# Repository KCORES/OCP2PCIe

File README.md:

# OCP2PCIe
 OCP 夹层网卡转标准 PCIe 槽转接卡设计  
 OCP Mezzanine card V2.0 to standard PCIe slot adapter design

 KCORES HomeLab 交流群 826702309

# For User
**用户指南**  

如果你想快速制作自己的OCP转接卡，请到[发行页面](https://github.com/KCORES/OCP2PCIe/releases)下载已发布的 Gerber 文件包  
并按[用户指南](doc/UserGuide_zh.md)准备相应的零件

If you want to build a OCP2PCIe card yourself quickly, Please visit [Release](https://github.com/KCORES/OCP2PCIe/releases) to download Gerber zip package  
More detail please bisit [User Guide](doc/UserGuide_zh.md).

# For Developer
**开发者指南**

**[Developer Guide Link](doc/DevGuide_zh.md)**

OCP2PCIe Lib has been updated, now you can create OCP2PCIe design easily.

# 最近动态

1. 正在制作 PCI 挡板的 CAD 图纸，  
不过考虑到小批量钣金加工的成本，可能只有等JS量产了
1. 上传了 OCP2PCIe Lib 现在可以更容易构建你自己的转接卡
1. 更新新版的ReadMe
2. 发布 V2.0Beta

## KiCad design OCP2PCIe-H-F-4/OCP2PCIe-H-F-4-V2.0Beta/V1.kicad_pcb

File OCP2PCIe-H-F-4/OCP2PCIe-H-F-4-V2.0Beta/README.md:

# V2.0 Beta ChangeLog

使用OCP标准库

重新布线

螺丝孔覆铜

单面放置元件

添加切成10x10以内的版本

刷新了版本号

# V1.1 Beta ChangeLog

修正鬼畜布线

覆铜

优化螺丝孔

刷新了版本号

添加切成10x10以内的版本

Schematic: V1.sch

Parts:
C1: C; CP_Elec_6.3x5.4
C2: C; CP_EIA-7343-31_Kemet-D
C3, C4: C; C_1206_3216Metric
J1: PCI Express x4; BUS_PCIexpress_x4
J2: Conn_02x40_Top_Bottom; OCP_Mezz_V2.0
J3, J4: Conn_01x02; PinHeader_1x02_P2.54mm_Vertical
TP1: TestPoint_2Pole; TestPlot
U1: DM02

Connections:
3V3AUX: J1.B10, J2.7, J2.66
+3V3: J1.A9, J1.A10, J1.B8, J2.10, J2.11, J2.12, J2.13, J2.69, J2.70, J2.71, J2.72
+12V: C1.1, J1.A2, J1.A3, J1.B1, J1.B2, J1.B3, J2.61, J2.62, J2.63, J3.1, TP1.1, U1.4
GND: C1.2, C2.2, C3.2, C4.2, J1.A4, J1.A12, J1.A15, J1.A18, J1.A20, J1.A23, J1.A24, J1.A27, J1.A28, J1.A31, J1.B4, J1.B7, J1.B13, J1.B16, J1.B18, J1.B21, J1.B22, J1.B25, J1.B26, J1.B29, J1.B32, J2.5, J2.6, J2.8, J2.9, J2.20, J2.21, J2.24, J2.25, J2.28, J2.29, J2.32, J2.33, J2.36, J2.37, J2.40, J2.41, J2.44, J2.45, J2.48, J2.49, J2.52, J2.53, J2.56, J2.57, J2.60, J2.64, J2.65, J2.67, J2.68, J2.73, J2.79, J2.82, J2.83, J2.86, J2.87, J2.90, J2.91, J2.94, J2.95, J2.98, J2.99, J2.102, J2.103, J2.106, J2.107, J2.110, J2.111, J2.114, J2.115, J2.118, J2.119, J3.2, J4.2, U1.2, U1.3
HSI0_N: J1.A17, J2.31
HSI0_P: J1.A16, J2.30
HSI1_N: J1.A22, J2.35
HSI1_P: J1.A21, J2.34
HSI2_N: J1.A26, J2.39
HSI2_P: J1.A25, J2.38
HSI3_N: J1.A30, J2.43
HSI3_P: J1.A29, J2.42
HSO0_N: J1.B15, J2.89
HSO0_P: J1.B14, J2.88
HSO1_N: J1.B20, J2.93
HSO1_P: J1.B19, J2.92
HSO2_N: J1.B24, J2.97
HSO2_P: J1.B23, J2.96
HSO3_N: J1.B28, J2.101
HSO3_P: J1.B27, J2.100
P5V_AUX: C2.1, C3.1, C4.1, J2.2, J2.3, J2.4, J4.1, TP1.2, U1.1
PERST: J1.A11, J2.17
PRSNT1: J1.A1, J2.1
PRSNT2: J1.B31, J2.120
REFCLK+: J1.A13, J2.84
REFCLK-: J1.A14, J2.85
WAKE: J1.B11, J2.77

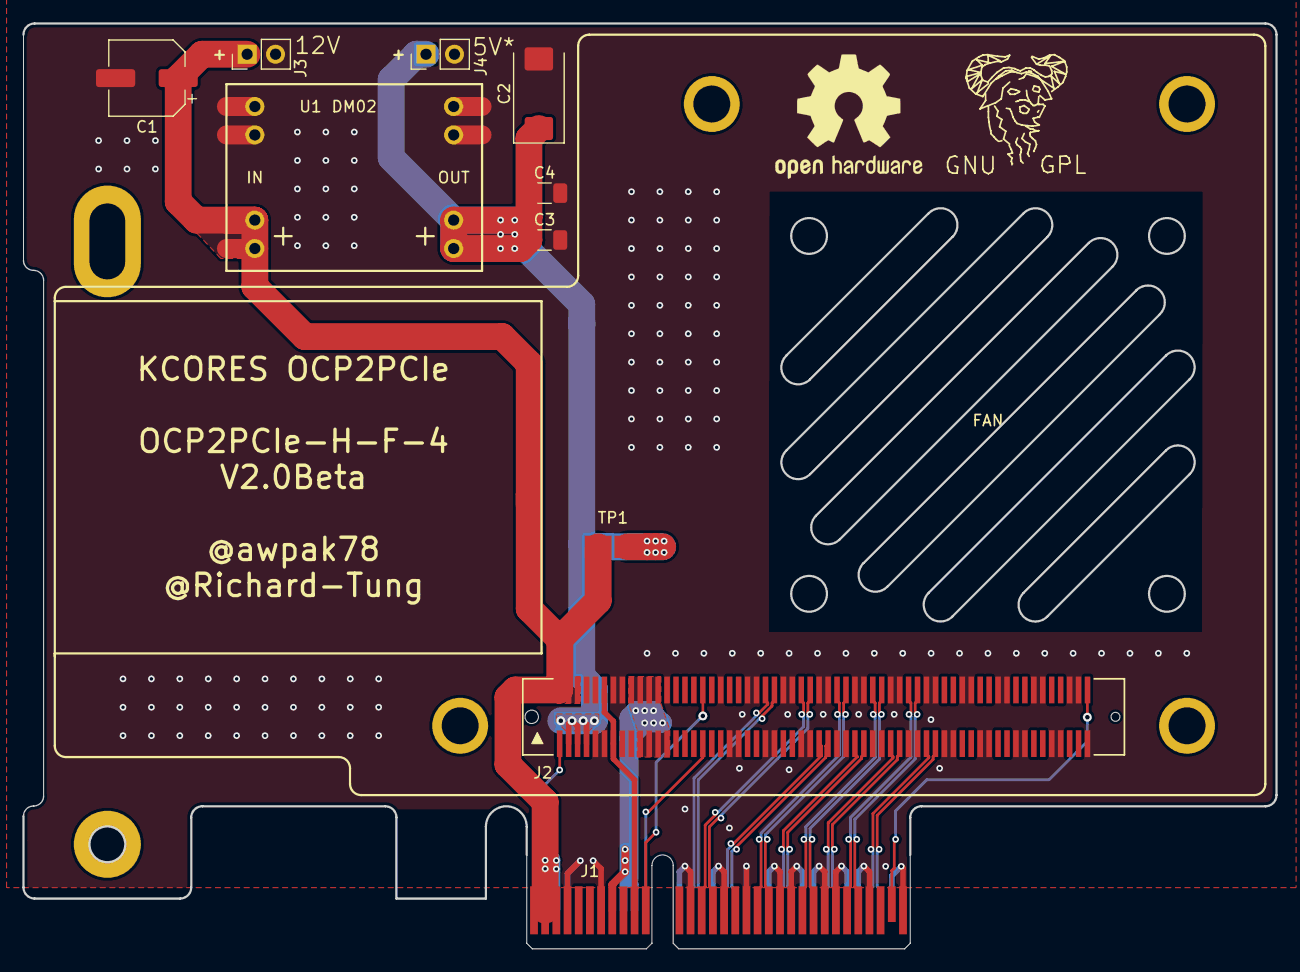
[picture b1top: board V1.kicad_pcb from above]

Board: 2 copper layers, 112.1 x 82.8 mm, 11 parts (0 on the bottom side), 27 nets.

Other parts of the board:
FAN: Fan_4010

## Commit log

2020-03-17 #61 ntel? -> Intel？
2020-03-18 Update OSHW and GNU Logo
2020-03-19 Update V1.0 Beta
2020-03-19 Update V1.0B readme
2020-03-20 Fix Readme
2020-03-21 Update OCP2PCIe Lib
2020-03-26 v1.1 update
2020-03-27 v1.1: add 10x10 cut version
2020-03-27 Create 3D model
2020-03-27 Add 3D_modle
    包含图纸，说明文档
2020-03-27 fix image
2020-04-18 v2.0 beta
2020-04-18 add new model
